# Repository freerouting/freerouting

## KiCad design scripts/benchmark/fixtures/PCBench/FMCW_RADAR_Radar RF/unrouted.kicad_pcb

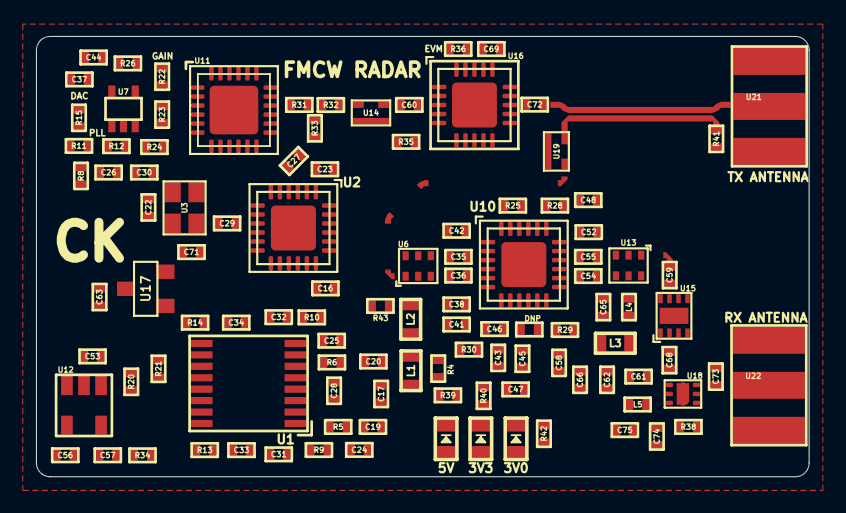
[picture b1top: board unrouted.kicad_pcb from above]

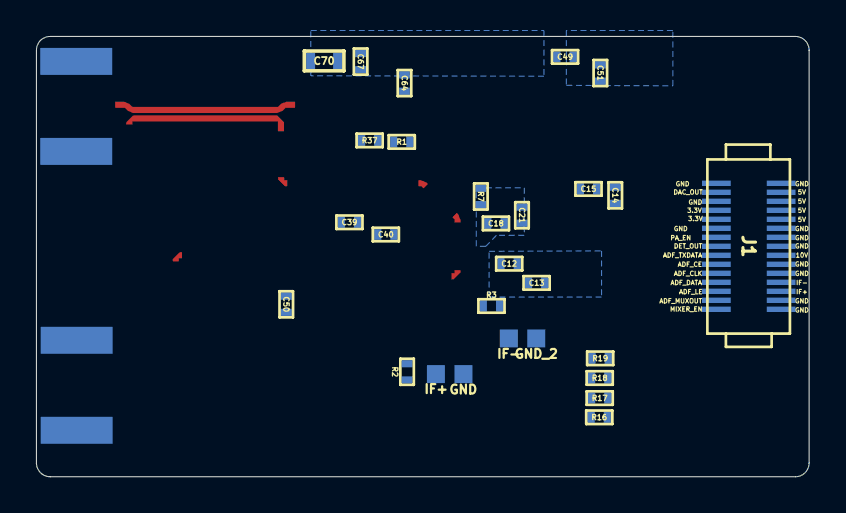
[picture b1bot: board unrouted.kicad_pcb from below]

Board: 4 copper layers, 42.9 x 24.5 mm, 143 parts (28 on the bottom side), 92 nets, no tracks yet.

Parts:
3V0, 3V3, 5V: Led_Diode; Diode_0603
C12, C13, C14, C21, C22, C28, C37, C38, C39, C40, C43, C45, C46, C48, C50, C51, C52, C53, C64, C67, C69, C74, C75: 100nF; SMD_0402
C15, C16, C18, C59, C68: 18pF; SMD_0402
C17: 2.2nF; SMD_0402
C19, C20, C26: 330nF; SMD_0402
C23, C41, C42, C47, C65: 100pF; SMD_0402
C24, C25, C35, C36, C54, C55, C62: 10pF; SMD_0402
C27: 2pF; SMD_0402
C29, C31, C32, C33, C34, C44: 470pF; SMD_0402
C30, C56, C61: 10nF; SMD_0402
C49, C57, C63, C71: 2.2uF; SMD_0402
C58, C66: DNP; SMD_0402
C60, C72: 1000pF; SMD_0402
C70: 10uF; SMD_0603
C73: 0.5pF; SMD_0402
DNP: DNP; SMD_0402
GND: GND; SolderPad_1_1.5mm_SMD_Rectangle
GND_2: GND; SolderPad_1_1.5mm_SMD_Rectangle
IF+: IF+_PAD; SolderPad_1_1.5mm_SMD_Rectangle
IF-: IF-_PAD; SolderPad_1_1.5mm_SMD_Rectangle
J1: Connector_02x15; PinHeader_2x15_DF12B(5.0)-30DP-0.5V(86)
L1, L2: 2.2uH; SMD_0603
L3: BLM18PG181SN1D; SMD_0603
L4: LQW15AN9N9J80D; SMD_0402
L5: 0.6nH; SMD_0402
R1, R16, R19, R29, R39, R40, R42: 1K; SMD_0402
R2, R3, R15, R30: DNP; SMD_0402
R4, R12, R22, R35, R43: 0; SMD_0402
R5, R6: 549; SMD_0402
R7: 5.49K; SMD_0402
R8: 69.8; SMD_0402
R9, R10, R34: 10K; SMD_0402
R11: 240; SMD_0402
R13, R14: 910; SMD_0402
R17, R18: 130; SMD_0402
R20, R21: 4.99K; SMD_0402
R23, R24, R26: 4.7K; SMD_0402
R25, R28, R41: 50; SMD_0402
R31, R32, R33: 18; SMD_0402
R36: 0 to 27; SMD_0402
R37: 30K; SMD_0402
R38: 100; SMD_0402
U1: LT6232; SSOP16_3.9x4.9mm_P0.635mm
U2: ADF4158; LFCSP24_4x4mm_P0.5mm_1EXP_2.5x2.5mm
U3: SG-210STF; Crystal_2.5x2mm
U4, U9, U23: MITERED_BEND; Mitered_Bend_0.34mm_90
U5: MITERED_BEND; Mitered_Bend_0.34mm_45
U6, U13: 5400BL15B050E; Balun_5400BL15B050E
U7: TLV172; SC70_5
U8: MITERED_BEND; Mitered_Bend_0.34mm_45_Mirrored
U10: ADL5801; LFCSP24_4x4mm_P0.5mm_1EXP_2.5x2.5mm
U11: HMC431LP4; QFN24_4x4mm_P0.5mm_1EXP_2.7x2.7mm
U12: LDS3985; SOT23_5
U14, U19: PAT1220-C-6DB; PAT1220_6dB
U15: TRF37A73; WSON8_2x2mm_P0.5mm_1EXP_0.9x1.6mm
U16: TQP5523; QFN20_4x4mm_P0.5mm_1EXP_2.5x2.5mm
U17: MCP1700; SOT23_3
U18: SKY65404; SKY65404_31
U20: Directional_Coupler; Directional_Coupler_15dB
U21, U22: SMA_Connector

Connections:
25MHz: C29.1, U2.9
+2V5: C57.1, R16.2, R17.2, R18.1, R19.2, R34.1, U1.3, U1.5, U12.5
+3V0: 3V0.2, C49.1, C51.1, C58.1, C71.1, C74.1, C75.1, L3.1, L5.2, R38.1, U11.20, U17.2
+3V3: 3V3.2, C12.1, C13.1, C14.1, C15.1, C16.1, C22.1, C53.1, C63.1, J1.4, J1.5, U2.6, U2.7, U2.8, U2.18, U2.19, U3.1, U3.4, U12.1, U12.3, U17.3
+5V: 5V.2, C18.1, C21.1, C28.2, C38.2, C39.2, C40.2, C41.2, C42.2, C48.2, C50.2, C52.1, C67.2, C69.2, C70.2, J1.26, J1.27, J1.28, J1.29, R25.1, R28.2, R29.1, R36.1, U1.4, U2.22, U10.7, U10.13, U10.18, U10.24, U16.18, U16.19
+10V: C37.1, J1.22, U7.5
ADF_CE: J1.10, U2.13
ADF_CLK: J1.11, U2.14
ADF_DATA: J1.12, U2.15
ADF_LE: J1.13, U2.16
ADF_MUXOUT: J1.14, U2.17
ADF_TXDATA: J1.9, U2.12
DAC_OUT1: J1.2, R15.1
DET_OUT: J1.8, R37.1, U16.10
GND: C12.2, C13.2, C14.2, C15.2, C16.2, C18.2, C21.2, C22.2, C23.2, C28.1, C30.2, C37.2, C38.1, C39.1, C40.1, C41.1, C42.1, C43.1, C44.2, C45.1, C46.1, C47.1, C48.1, C49.2, C50.1, C51.2, C52.2, C53.2, C56.2, C57.2, C58.2, C61.2, C62.2, C63.2, C64.2, C65.2, C66.2, C67.1, C69.1, C70.1, C71.2, C73.2, C74.2, C75.2, GND.1, GND_2.1, J1.1, J1.3, J1.6, J1.16, J1.17, J1.20, J1.21, J1.23, J1.24, J1.25, J1.30, R1.2, R7.2, R11.1, R24.2, R30.2, R34.2, R37.2, R39.2, R40.2, R41.2, R42.2, U1.13, U2.1, U2.2, U2.3, U2.10, U2.11, U2.25, U3.2, U6.2, U6.5, U7.2, U10.1, U10.2, U10.5, U10.6, U10.8, U10.12, U10.14, U10.17, U10.19, U10.23, U10.25, U11.15, U11.25, U12.2, U13.2, U13.5, U14.3, U15.3, U15.4, U15.5, U15.6, U15.8, U15.9, U16.1, U16.2, U16.4, U16.11, U16.12, U16.14, U16.15, U16.16, U16.17, U16.21, U17.1, U18.2, U18.5, U18.7, U19.3, U21.2, U21.3, U21.4, U21.5, U22.2, U22.3, U22.4, U22.5
IF+: R2.1, R4.1, R28.1, U10.20
IF-: R3.2, R25.2, R43.2, U10.21
IFN_Filtered: J1.19, R14.2, R21.1, U1.10
IFP_Filtered: J1.18, R13.1, R20.1, U1.16
MIXER_ENB: J1.15, U10.9
MIXER_LO: U4.2, U6.1
unnamed: C17.1, C19.2, L1.2
unnamed: C17.2, C20.2, L2.2
unnamed: C19.1, R5.1
unnamed: C20.1, R6.1
unnamed: C23.1, U2.4
unnamed: C24.1, C31.2, R9.2, U1.1
unnamed: C24.2, R5.2, R9.1, U1.2
unnamed: C25.1, C32.2, R10.2, U1.7
unnamed: C25.2, R6.2, R10.1, U1.6
unnamed: C26.1, C30.1, R12.1, U2.24
unnamed: C26.2, R8.2, R11.2
unnamed: C27.1, U2.5
unnamed: C27.2, R33.2
unnamed: C29.2, U3.3
unnamed: C31.1, C33.2, R13.2
unnamed: C32.1, C34.2, R14.1
unnamed: C33.1, R17.1, U1.14
unnamed: C34.1, R18.2, U1.12
unnamed: C35.1, U10.3
unnamed: C35.2, U6.4
unnamed: C36.1, U10.4
unnamed: C36.2, U6.3
unnamed: C43.2, C46.2, DNP.2, R29.2, R30.1, U10.10
unnamed: C44.1, R26.1, U11.22
unnamed: C45.2, C47.2, DNP.1, U10.11
unnamed: C54.1, U13.4
unnamed: C55.1, U13.3
unnamed: C56.1, U12.4
unnamed: C59.1, L4.1, U15.7
unnamed: C59.2, U23.1
unnamed: C60.1, U16.3
unnamed: C60.2, U14.2
unnamed: C61.1, C62.1, C65.1, C66.1, L3.2, L4.2, U15.1
unnamed: C64.1, R36.2, U16.20
unnamed: C68.1, U18.4
unnamed: C68.2, U15.2
unnamed: C72.1, U20.1
unnamed: C72.2, U16.13
unnamed: C73.1, U18.3, U22.1
unnamed: 5V.1, R39.1
unnamed: 3V3.1, R40.1
unnamed: 3V0.1, R42.1
unnamed: L1.1, R4.2
unnamed: L2.1, R43.1
unnamed: L5.1, U18.6
unnamed: R1.1, R35.2, U16.5
unnamed: IF+.1, R2.2
unnamed: IF-.1, R3.1
unnamed: R7.1, U2.23
unnamed: R8.1, U2.20
unnamed: R12.2, R15.2, U7.1
unnamed: R16.1, R20.2, U1.15
unnamed: R19.1, R21.2, U1.11
unnamed: R22.1, R26.2, U7.4
unnamed: R22.2, R23.1
unnamed: R23.2, R24.1, U7.3
unnamed: R31.1, U11.16
unnamed: R31.2, R32.2, R33.1
unnamed: R32.1, U14.1
unnamed: R38.2, U18.1
unnamed: R41.1, U20.4
unnamed: U4.1, U8.1
unnamed: U5.1, U9.1
unnamed: U5.2, U8.2
unnamed: U13.1, U23.2
unnamed: U19.1, U20.3
unnamed: U9.2, U19.2
unnamed: U20.2, U21.1
PA_EN: J1.7, R35.1
RFIN: C54.2, U10.15
RFIP: C55.2, U10.16

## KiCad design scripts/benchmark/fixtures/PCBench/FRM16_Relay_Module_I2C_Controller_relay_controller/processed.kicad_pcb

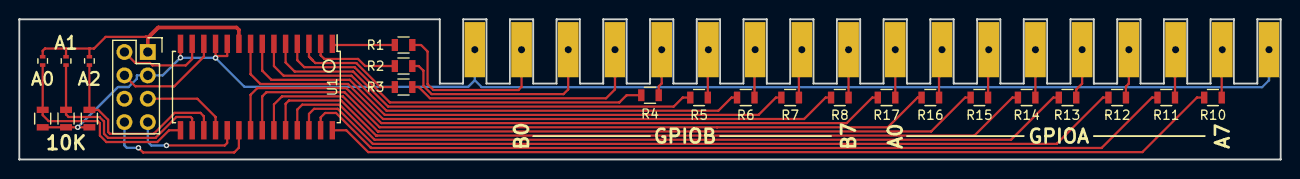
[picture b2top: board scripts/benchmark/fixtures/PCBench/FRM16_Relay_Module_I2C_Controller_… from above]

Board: 2 copper layers, 137.2 x 15.2 mm, 30 parts (0 on the bottom side), 42 nets.

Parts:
JP1, JP2, JP3: Jumper_NO_Small; R_0402
P1, P2, P3, P4, P5, P6: CONN_01X03; card_edge_3_conductor
P7: CONN_02X04; Socket_Strip_Straight_2x04
R1, R2, R3, R4, R5, R6, R7, R8, R9, R10, R11, R12, R13, R14, R15, R16, R17, R18, R19: R; R_0805
U1: MCP23017; SOIC-28_7.5x17.9mm_Pitch1.27mm

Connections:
GND: P1.1, P4.1, P7.3, R9.2, R18.2, R19.2, U1.10, U1.11, U1.14
INTA: P7.8, U1.20
INTB: P7.7, U1.19
unnamed: JP1.2, R19.1, U1.17
unnamed: JP2.2, R18.1, U1.16
unnamed: JP3.2, R9.1, U1.15
unnamed: P1.2, R1.2
unnamed: P1.3, R2.2
unnamed: P2.1, R3.2
unnamed: P2.2, R4.2
unnamed: P2.3, R5.2
unnamed: P3.1, R6.2
unnamed: P3.2, R7.2
unnamed: P3.3, R8.2
unnamed: P4.2, R10.1
unnamed: P4.3, R11.1
unnamed: P5.1, R12.1
unnamed: P5.2, R13.1
unnamed: P5.3, R14.1
unnamed: P6.1, R15.1
unnamed: P6.2, R16.1
unnamed: P6.3, R17.1
unnamed: R1.1, U1.1
unnamed: R2.1, U1.2
unnamed: R3.1, U1.3
unnamed: R4.1, U1.4
unnamed: R5.1, U1.5
unnamed: R6.1, U1.6
unnamed: R7.1, U1.7
unnamed: R8.1, U1.8
unnamed: R10.2, U1.28
unnamed: R11.2, U1.27
unnamed: R12.2, U1.26
unnamed: R13.2, U1.25
unnamed: R14.2, U1.24
unnamed: R15.2, U1.23
unnamed: R16.2, U1.22
unnamed: R17.2, U1.21
SCL: P7.4, U1.12
SDA: P7.2, U1.13
VCC: JP1.1, JP2.1, JP3.1, P7.1, U1.9
~RST: P7.5, U1.18

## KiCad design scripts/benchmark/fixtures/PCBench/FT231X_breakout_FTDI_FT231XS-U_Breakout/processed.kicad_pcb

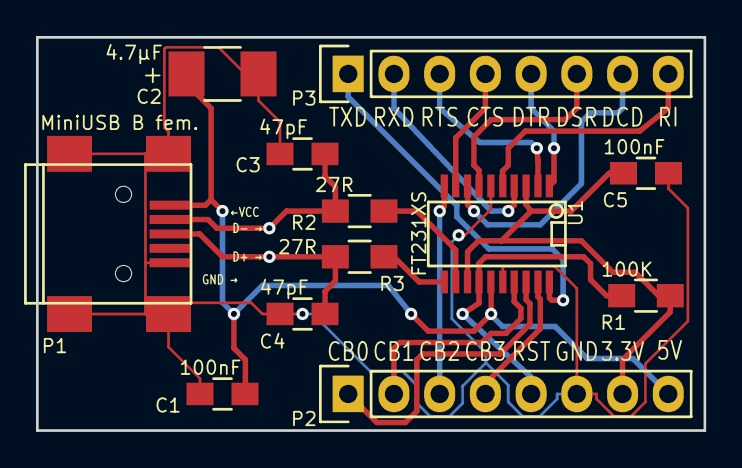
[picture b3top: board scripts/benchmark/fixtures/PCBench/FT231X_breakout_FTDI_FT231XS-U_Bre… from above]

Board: 2 copper layers, 37.1 x 21.8 mm, 12 parts (0 on the bottom side), 20 nets.

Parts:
C1, C5: 100nF; C_0805_HandSoldering
C2: 4.7µF; C_1210_HandSoldering
C3, C4: 47pF; C_0805_HandSoldering
P1: MiniUSB B fem.; USB_Mini-B
P2, P3: CONN_01X08; Pin_Header_Straight_1x08
R1: 100K; R_0805_HandSoldering
R2, R3: 27R; R_0805_HandSoldering
U1: FT231XS; SSOP-20

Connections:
CBUS0: P2.1, U1.18
CBUS1: P2.2, U1.17
CBUS2: P2.3, U1.10
CBUS3: P2.4, U1.19
CTS: P3.4, U1.9
DCD: P3.7, U1.8
DSR: P3.6, U1.7
DTR: P3.5, U1.1
GND: C1.2, C2.2, C3.2, C4.2, C5.1, P1.5, P1.6, P2.6, U1.6, U1.16
unnamed: C3.1, P1.2, R2.2
unnamed: C4.1, P1.3, R3.2
unnamed: R2.1, U1.12
unnamed: R3.1, U1.11
RESET: P2.5, R1.2, U1.14
RI: P3.8, U1.5
RTS: P3.3, U1.2
RXD: P3.2, U1.4
TXD: P3.1, U1.20
VCC: C1.1, C2.1, P1.1, P2.8, U1.15
VCCIO: C5.2, P2.7, R1.1, U1.3, U1.13

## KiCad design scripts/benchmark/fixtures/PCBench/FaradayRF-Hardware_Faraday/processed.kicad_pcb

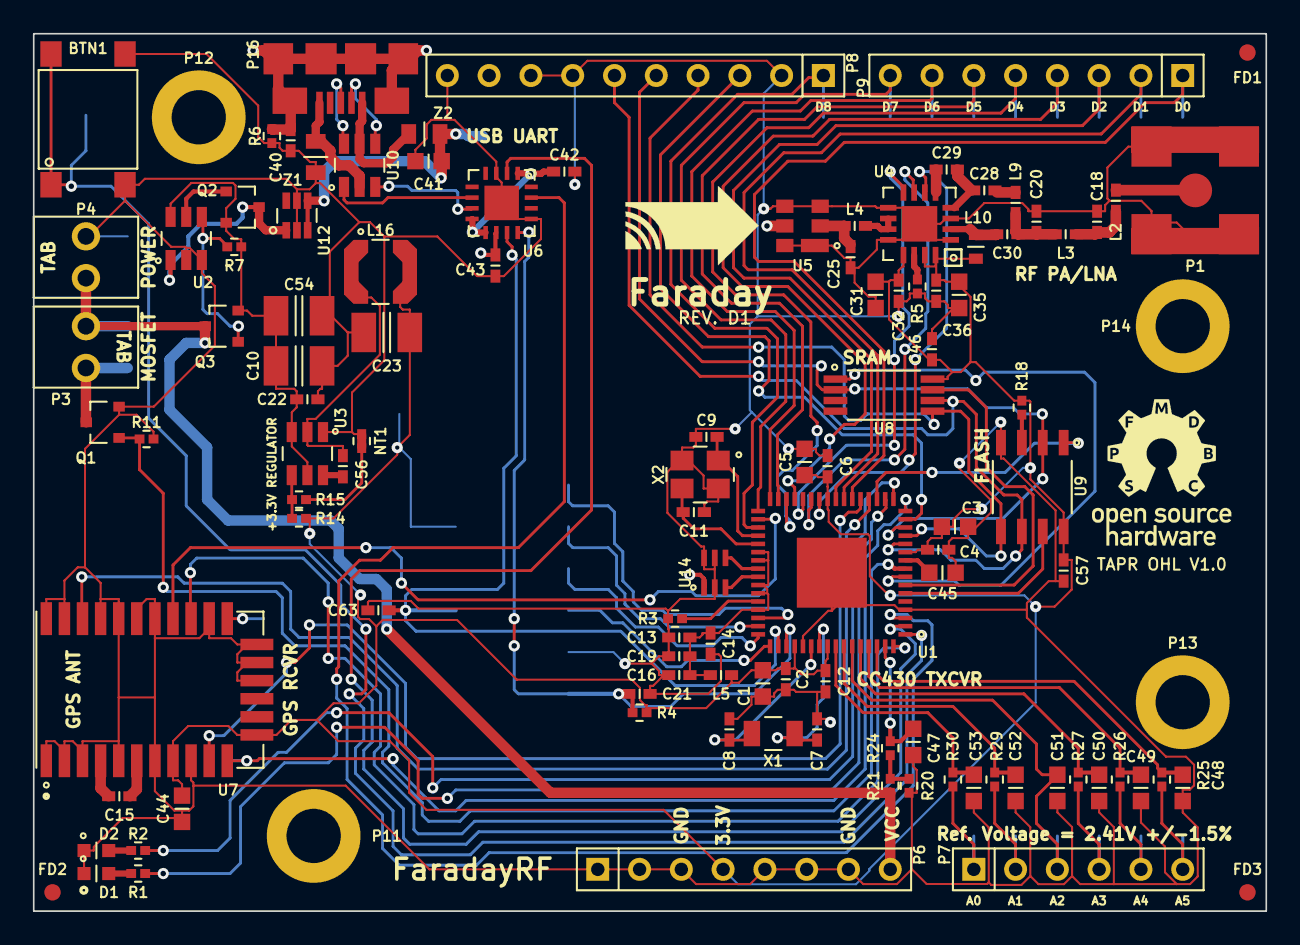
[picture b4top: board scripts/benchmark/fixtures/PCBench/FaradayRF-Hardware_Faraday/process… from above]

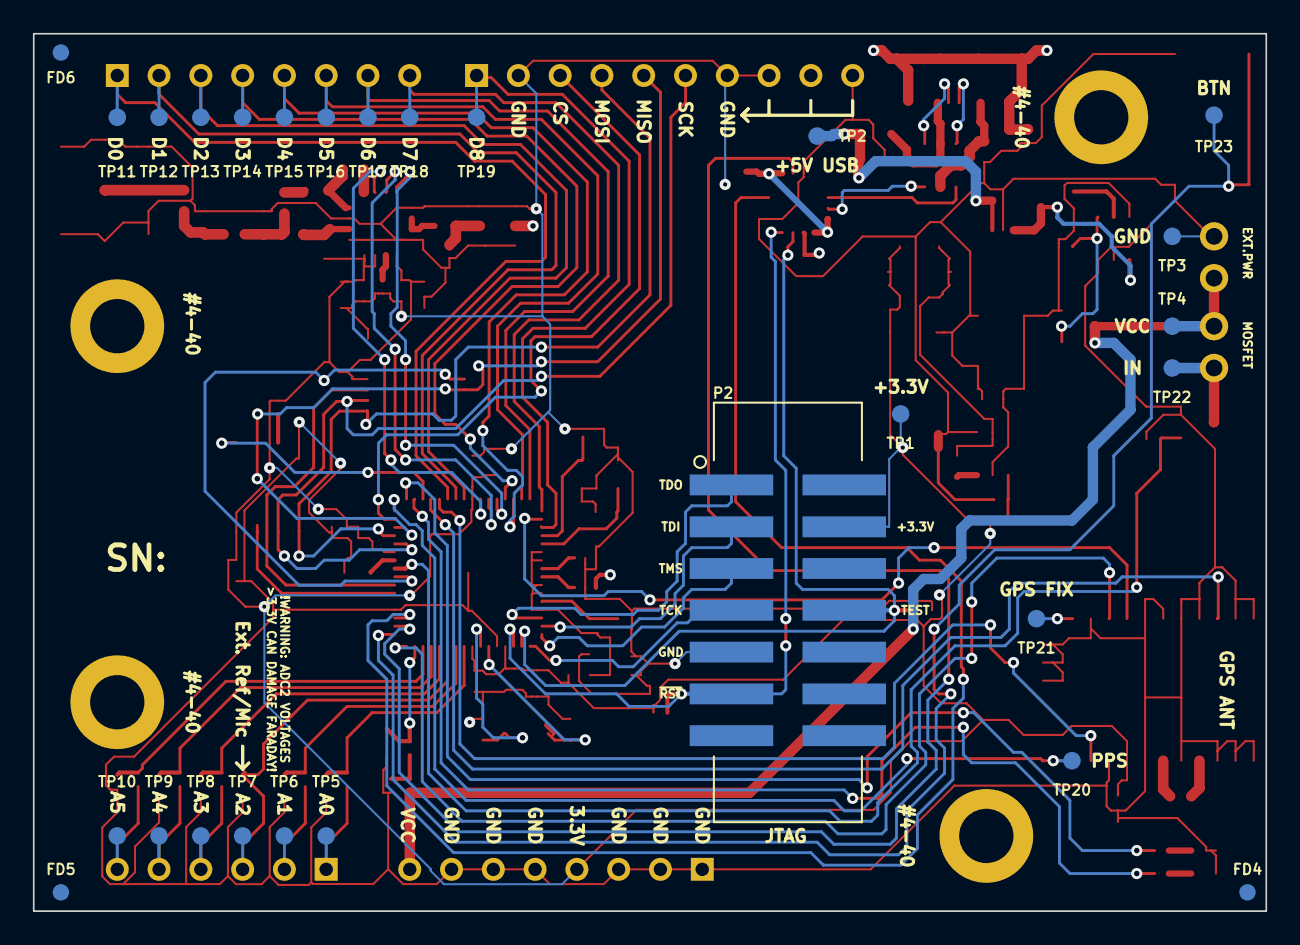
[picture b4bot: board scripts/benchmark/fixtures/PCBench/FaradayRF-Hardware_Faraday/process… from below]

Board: 4 copper layers, 74.9 x 53.3 mm, 141 parts (27 on the bottom side), 97 nets.

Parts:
BTN1: DNP; PTS645-SMD
C1, C3, C5, C31, C35, C41, C44, C47, C48, C49, C50, C52, C53: 1uF; C0603
C2, C4, C6, C12, C13, C16, C32, C36, C40, C42, C43, C46, C56: 0.1uF; C0402
C7, C8, C22, C57: DNP; C0402
C9, C11: 30pF; C0402
C10, C54: 10uF; C1210
C14, C15, C19, C28, C29, C63: 12pF; C0402
C18: 7.5pF; C0402
C20: 3.3pF; C0402
C21: 2.2nF; C0402
C23: 47uF; C1210
C25: 0.8pF; C0402
C30: 47pF; C0402
C45: 470nF; C0603
C51: DNP; C0603
D1, D2: LED-IPC; LGL29K
FD1, FD2, FD3, FD4, FD5, FD6: FIDUCIAL; FD1
G1: OSHW
G2: FARADAYRF; faradayRF
L2: 9.1nH; L0402
L3: 2.9nH; L0402
L4: 10nH; L0402
L5: BLM15HG102SN1D; L0402
L9: 7.5nH; L0402
L10: 22nH; L0603
L16: 4.7uH; LPS4018
NT1: NETTIE; NETTIE-0402
P1: RF_FEMALE; CONSMA001-SMD-G
P2: DNP; 2514-6002UB
P3, P4: 22232021
P6, P9: DNP; SIL-8
P7: DNP; SIL-6
P8: DNP; SIL-10
P11, P12, P13, P14: DNP; MTH-4-40-Tight
P16: USB-MICRO-B; 10118192-0001LF
Q1: IRLML6346TRPBF; SOT23-NXP
Q2, Q3: PMV48XP; SOT23-NXP
R1, R2: 360; R0402
R3, R4, R7: 56K; R0402
R5, R20: 3.3K; R0402
R6: 1M; R0402
R11, R15, R24, R25, R26, R27, R29, R30: 10K; R0402
R14, R21: 33.2K; R0402
R18: DNP; R0402
TP1, TP2, TP3, TP4, TP5, TP6, TP7, TP8, TP9, TP10, TP11, TP12, TP13, TP14, TP15, TP16, TP17, TP18, TP19, TP20, TP21, TP22, TP23: TEST-POINT; TEST-POINT-42MIL
U1: CC430F6137; RGC
U2: LTC4412; TSOT23-6
U3: TPS562201DDCR; TSOT23-6
U4: CC1190; RGV
U5: SF2049E
U6: FT230XQ-R; QFN-16-4x4
U7: M10478-A2
U8: 23K256T-I/ST; TSSOP8
U9: DNP; SOIC8-150MIL
U10: NUF2101MT1G; TSOT23-6
U12: MIC94072YC6; SC70-6
U14: 0915BM15A0001E
X1: ST3215SB32768H5HPWAA
X2: ABM8G-26.000MHZ-18-D2Y-T; ABM8G
Z1, Z2: MI0805K400R-10; L0805

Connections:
+3.3V: C1.1, C2.1, C3.1, C4.1, C5.1, C6.1, C12.1, C23.1, C31.2, C32.2, C35.2, C36.2, C44.1, C46.1, C57.1, L5.2, L10.1, L16.2, P2.4, P6.4, R4.1, R14.1, R18.2, TP1.1, U1.11, U1.25, U1.52, U1.56, U4.13, U4.15, U4.16, U7.8, U7.12, U8.8, U9.8
+5V: C41.1, C43.1, TP2.1, U6.10, U12.3, U12.4, Z2.2
/CC430/DIGITAL_IO_0: P9.1, TP11.1, U1.22
/CC430/DIGITAL_IO_1: P9.2, TP12.1, U1.23
/CC430/DIGITAL_IO_2: P9.3, TP13.1, U1.24
/CC430/DIGITAL_IO_3: P9.4, TP14.1, U1.29
/CC430/DIGITAL_IO_4: P9.5, TP15.1, U1.30
/CC430/DIGITAL_IO_5: P9.6, TP16.1, U1.31
/CC430/DIGITAL_IO_6: P9.7, TP17.1, U1.32
/CC430/DIGITAL_IO_7: P9.8, TP18.1, U1.33
/CC430/DIGITAL_IO_8: P8.1, TP19.1, U1.35
/CC430/GPS-PPS: TP20.1, U1.16, U7.11
/CC430/GPS-RX: U1.34, U7.21
/CC430/GPS-TX: U1.64, U7.20
/CC430/MEM ~CS0~: U1.8, U8.1
/CC430/MEM ~CS1~: U1.19, U9.1
/CC430/MEM ~HOLD0~: U1.7, U8.7
/CC430/MEM ~HOLD1~: U1.6, U9.7
/CC430/MOSFET_CNTL: Q1.1, R11.1, U1.9
/CC430/P1_7: BTN1.1, BTN1.2, TP23.1, U1.1
/CC430/P2_1: C47.1, R24.2, U1.63
/CC430/P2_2: C48.1, R25.2, U1.62
/CC430/P2_3: C49.1, R26.2, U1.61
/CC430/P2_4: C50.1, R27.2, U1.60
/CC430/P2_6: C52.1, R29.2, U1.58
/CC430/P2_7: C53.1, R30.2, U1.57
/CC430/P3_6: R1.1, U1.18
/CC430/P3_7: R2.1, U1.17
/CC430/P5_0: C7.1, U1.55, X1.1
/CC430/P5_1: C8.1, U1.54, X1.2
/CC430/RF-PWR: C13.1, C14.1, C16.1, C19.1, L5.1, U1.38, U1.39, U1.42, U1.43, U1.45
/CC430/RF_N: U1.41, U14.3
/CC430/RF_P: U1.40, U14.4
/CC430/TCK: P2.7, U1.49
/CC430/TDI: P2.3, U1.47
/CC430/TDO: P2.1, U1.46
/CC430/TEST: C63.1, P2.8, U1.50, U6.11
/CC430/TMS: P2.5, U1.48
/CC430/~RST~: C21.1, P2.11, R4.2, U1.51, U6.12
/GPS/HRST: U1.21, U7.10
/GPS/STDBY: U1.20, U7.26
/Power Supply/3V3_SW: C56.2, L16.1, U3.2
/RF Front End/50Z-1: C25.1, L4.2, U5.2
/RF Front End/50Z-2: L4.1, U4.10, U4.11
/RF Front End/50Z_3: C30.2, L10.2, U4.2
/RF Front End/50Z_4: C20.1, C30.1, L3.2, L9.1
/RF Front End/50Z_5: C18.1, L2.2, L3.1
/RF Front End/CC1190-CC430-RF: U5.5, U14.1
/RF Front End/HGM_Select: U1.26, U4.6
/RF Front End/LNA_Enable: U1.27, U4.7
/RF Front End/PA_Enable: U1.28, U4.8
/RF Front End/RF_IN_OUT_Antenna: L2.1, P1.1
/Shield Connector/AD_0: P7.1, R30.1, TP5.1
/Shield Connector/AD_1: P7.2, R29.1, TP6.1
/Shield Connector/AD_2: C51.1, P7.3, TP7.1, U1.59
/Shield Connector/AD_3: P7.4, R27.1, TP8.1
/Shield Connector/AD_4: P7.5, R26.1, TP9.1
/Shield Connector/AD_5: P7.6, R25.1, TP10.1
/Shield Connector/CONN_CS: P8.3, U1.15
/Shield Connector/CONN_MISO/SCL: P8.5, U1.14, U8.2, U9.2
/Shield Connector/CONN_MOSI/SDA: P8.4, U1.13, U8.5, U9.5
/Shield Connector/CONN_SCK: P8.6, U1.12, U8.6, U9.6
/Shield Connector/MOSFET Channel/IN: P3.2, Q1.3, TP22.1
/Shield Connector/VCC-MON: R20.1, R21.2, R24.1
/USB to Serial/RXD: U1.2, U6.2
/USB to Serial/TXD: U1.3, U6.15
DGND: BTN1.3, BTN1.4, C1.2, C2.2, C3.2, C4.2, C5.2, C6.2, C7.2, C8.2, C9.2, C10.2, C11.2, C12.2, C13.2, C14.2, C16.2, C18.2, C19.2, C20.2, C21.2, C22.2, C23.2, C25.2, C31.1, C32.1, C35.1, C36.1, C40.2, C41.2, C42.2, C43.2, C44.2, C45.2, C46.2, C47.2, C48.2, C49.2, C50.2, C51.2, C52.2, C53.2, C54.2, C57.2, C63.2, D1.1, D2.1, NT1.1, P1.2, P2.9, P4.2, P6.1, P6.2, P6.3, P6.5, P6.6, P6.7, P8.2, P8.7, P8.8, P8.9, P8.10, Q1.2, R3.2, R5.2, R6.1, R11.2, R20.2, TP3.1, U1.4, U1.53, U1.65, U2.2, U2.3, U3.1, U4.1, U4.3, U4.9, U4.12, U4.17, U5.1, U5.3, U5.4, U5.6, U6.3, U6.13, U6.17, U7.1, U7.2, U7.3, U7.5, U7.7, U7.9, U7.15, U7.16, U7.17, U7.19, U7.22, U7.23, U7.24, U7.25, U7.27, U7.28, U9.4, U12.2, U12.5, U14.2, U14.5, U14.6, X2.2, X2.4, Z1.2
GNDPWR: C40.1, P11.1, P12.1, P13.1, P14.1, P16.6, R6.2
unnamed: C45.1, U1.10
unnamed: D1.2, R1.2
unnamed: D2.2, R2.2
unnamed: R3.1, U1.44
unnamed: C9.1, U1.36, X2.1
unnamed: C11.1, U1.37, X2.3
unnamed: C10.1, C22.1, C54.1, Q2.2, Q3.2, R7.1, U2.6, U3.3, U3.5
unnamed: C56.1, U3.6
unnamed: R14.2, R15.1, U3.4
unnamed: NT1.2, R15.2
unnamed: Q2.1, U2.5
unnamed: Q3.1, R7.2, U2.4
unnamed: Q2.3, U2.1, U12.1
unnamed: C28.2, C29.1, U4.4
unnamed: R5.1, U4.14
unnamed: C29.2, U4.5
unnamed: C28.1, L9.2
unnamed: P16.1, U10.5, Z2.1
unnamed: U6.6, U10.1
unnamed: P16.3, U10.6
unnamed: P16.2, U10.4
unnamed: U6.7, U10.3
unnamed: P16.5, U10.2, Z1.1
unnamed: C42.1, U6.1, U6.8, U6.9
unnamed: TP21.1, U7.18
unnamed: C15.2, U7.6
unnamed: C15.1, U7.4
unnamed: R18.1, U9.3
VCC: P3.1, P4.1, P6.8, Q3.3, R21.1, TP4.1
